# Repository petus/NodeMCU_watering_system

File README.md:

# NodeMCU_watering_system
Watering system for a few plants. The main component is WiFi module NodeMCU with ESP12E (ESP8266).<br>
The device contains two switching parts for pump/valve or another device. <br>
<br>
Websites:<br>
(CZ) https://chiptron.cz<br>
(EN) https://time4ee.com<br>
<br>
Important components: <br>
Relays (Coil Resistance 500 ohm, Nominal Coil Voltage 5 VDC, Switching Voltage 200 VDC, Switching Current 0.5 A) https://www.gme.cz/data/attachments/dsh.634-072.1.pdf <br>
<br>
Transistors (Ultra Low On-Resistance, N-Channel MOSFET, using for switching from GPIO) https://www.infineon.com/dgdl/irlml2502.pdf?fileId=5546d462533600a401535667f44d2602<br>
<br>
Description of device:<br>
NodeMCU watering system includes two outputs (through relays), it can switch water pump, valve or another device. NodeMCU contains one analog input for measurement of soil moisture.<br>
The device contains pin header for connecting of temperature/humidity sensor (by I2C) like Si7021, two LEDs which can be used for indication.<br>
The watering system can be powered by external power supply (the board contains 7805 voltage regulator).<br>

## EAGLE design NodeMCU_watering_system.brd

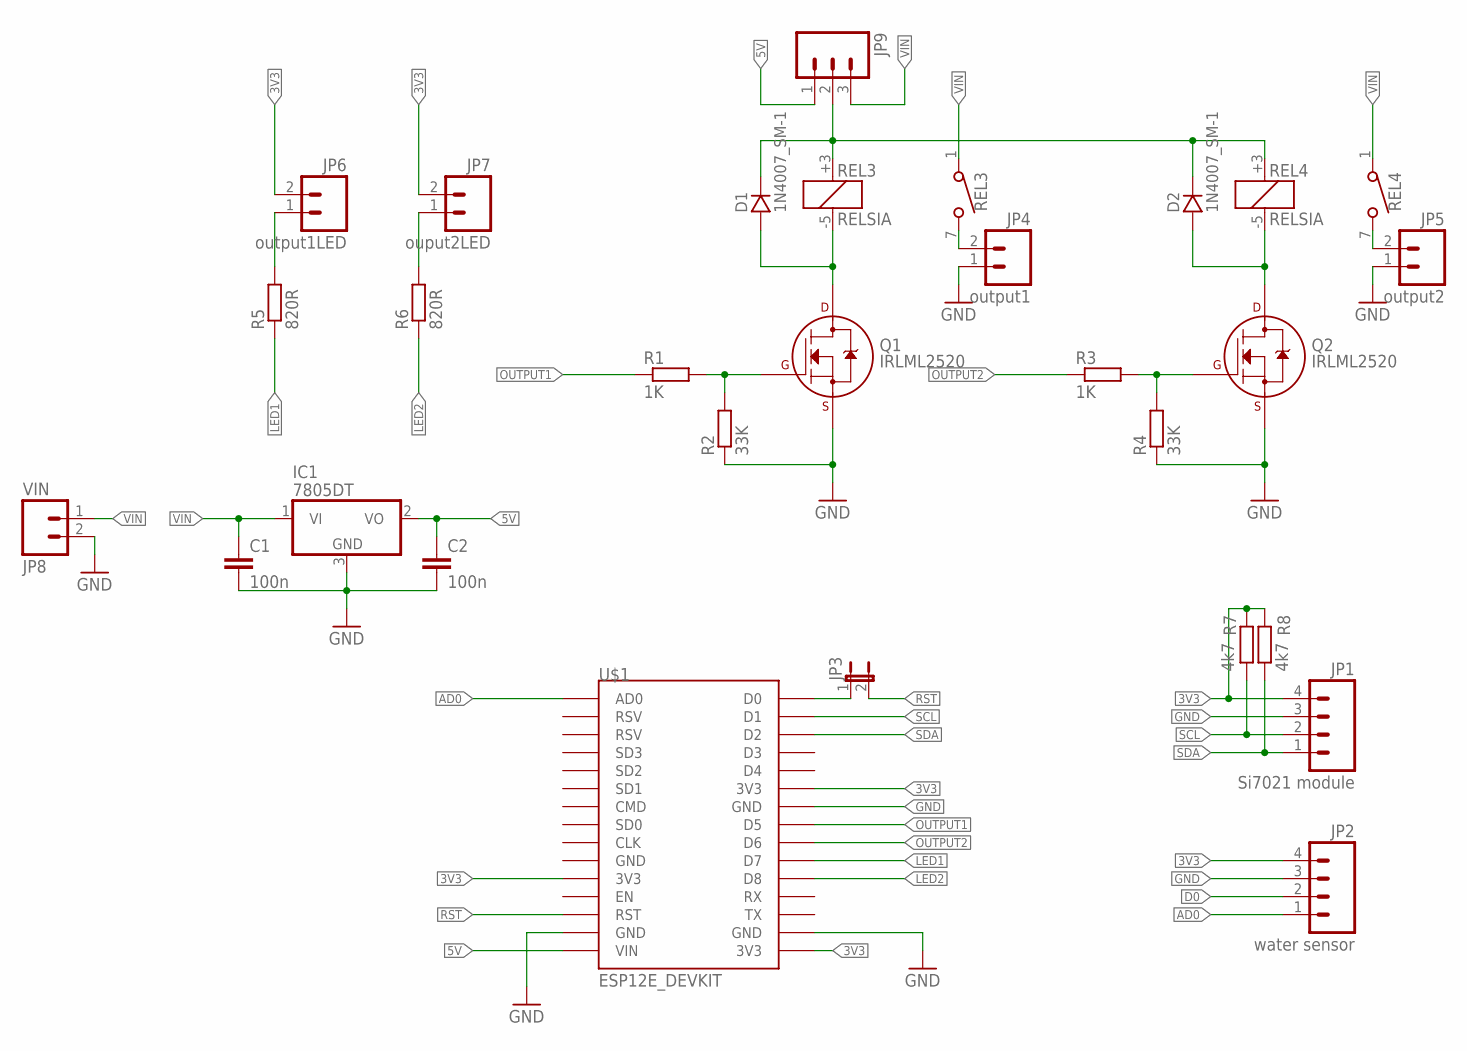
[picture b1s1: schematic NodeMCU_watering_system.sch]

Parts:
C1, C2: 100n; C0805K
D1, D2: 1N4007_SM-1; SM-1
IC1: 7805DT; TO252
JP1: Si7021 module; 1X04_LONGPADS
JP2: water sensor; 1X04_LONGPADS
JP3: JP1E; JP1
JP4: output1; 1X02_LOCK_LONGPADS
JP5: output2; 1X02_LOCK_LONGPADS
JP6: output1LED; 1X02_LOCK_LONGPADS
JP7: ouput2LED; 1X02_LOCK_LONGPADS
JP8: VIN; 1X02_LOCK_LONGPADS
JP9: M03LONGPADS; 1X03_LONGPADS
Q1, Q2: IRLML2520; SOT-23
R1, R3: 1K; M0805
R2, R4: 33K; M0805
R5, R6: 820R; M0805
R7, R8: 4k7; M0805
REL3, REL4: RELSIA
U$1: ESP12E_DEVKIT

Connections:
3V3: JP1.4, JP2.4, JP6.2, JP7.2, R7.2, R8.2, U$1.3V3@0 (3V3), U$1.3V3@1 (3V3), U$1.3V3@2 (3V3)
5V: C2.1, IC1.2 (VO), JP9.1, U$1.VIN
AD0: JP2.1, U$1.AD0
D0: JP2.2
GND: C1.2, C2.2, IC1.3 (GND), JP1.3, JP2.3, JP4.1, JP5.1, JP8.2, Q1.2 (S), Q2.2 (S), R2.1, R4.1, U$1.GND@1 (GND), U$1.GND@2 (GND), U$1.GND@3 (GND)
LED1: R5.1, U$1.D7
LED2: R6.1, U$1.D8
unnamed: JP3.1, U$1.D0
unnamed: Q1.1 (G), R1.2, R2.2
unnamed: Q2.1 (G), R3.2, R4.2
unnamed: D1.A, Q1.3 (D), REL3.-5 (C-)
unnamed: D2.A, Q2.3 (D), REL4.-5 (C-)
unnamed: JP4.2, REL3.7 (2)
unnamed: JP5.2, REL4.7 (2)
unnamed: JP6.1, R5.2
unnamed: JP7.1, R6.2
unnamed: D1.K, D2.K, JP9.2, REL3.+3 (C+), REL4.+3 (C+)
OUTPUT1: R1.1, U$1.D5
OUTPUT2: R3.1, U$1.D6
RST: JP3.2, U$1.RST
SCL: JP1.2, R7.1, U$1.D1
SDA: JP1.1, R8.1, U$1.D2
VIN: C1.1, IC1.1 (VI), JP8.1, JP9.3, REL3.1, REL4.1

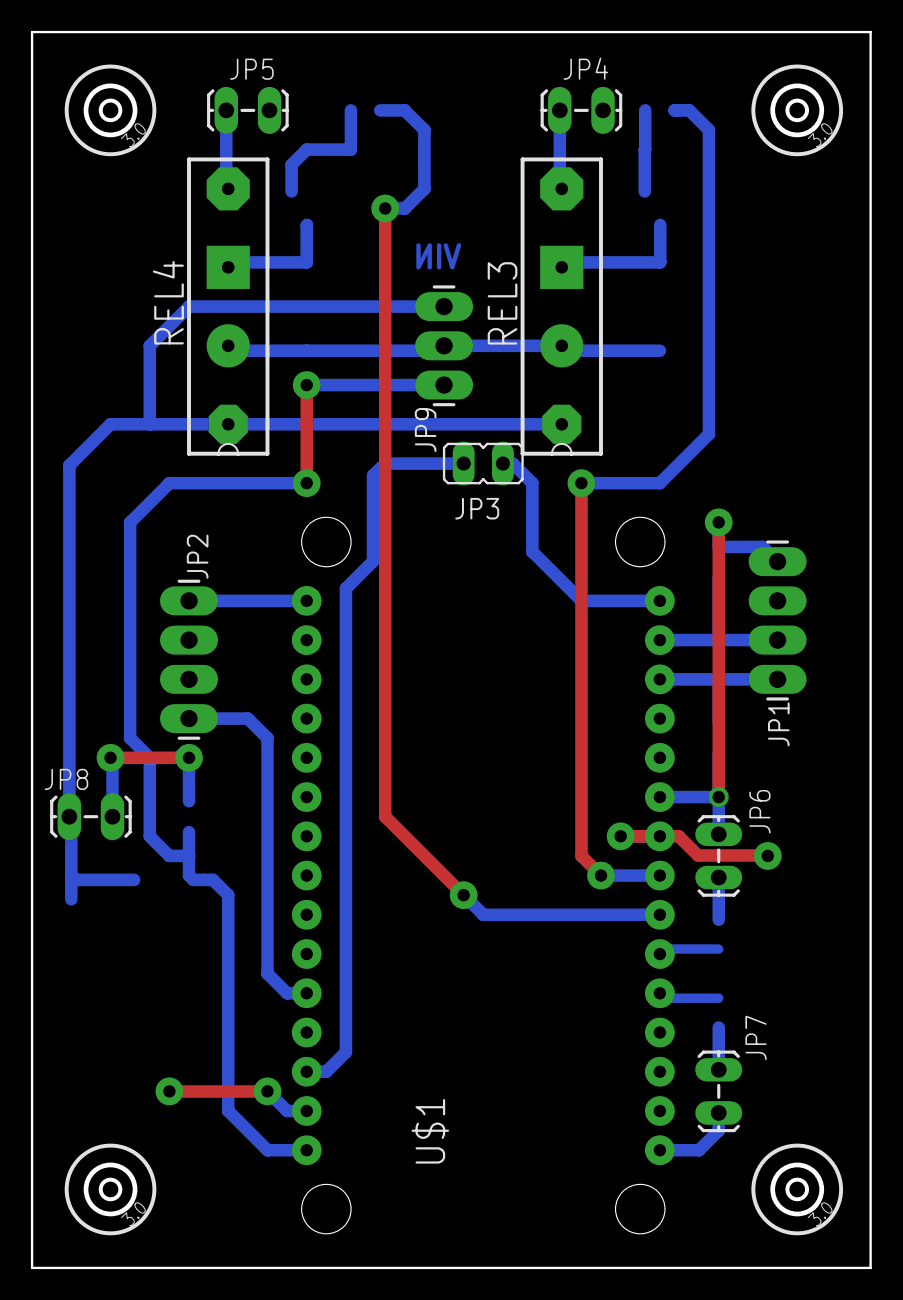
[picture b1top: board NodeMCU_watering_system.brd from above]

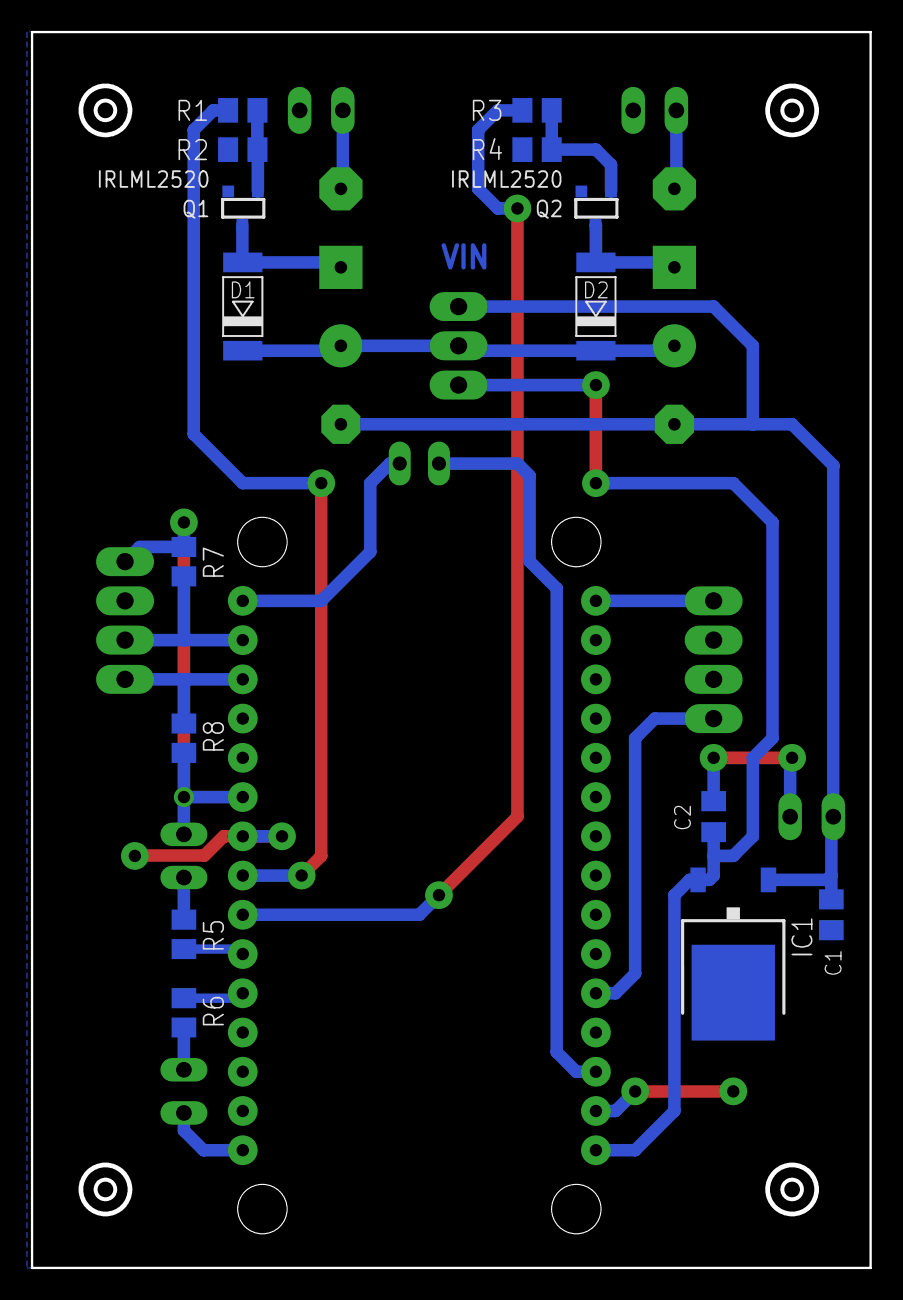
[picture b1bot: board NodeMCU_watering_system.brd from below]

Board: 2 copper layers, 54.1 x 79.8 mm, 31 parts (15 on the bottom side), 22 nets.

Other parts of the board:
U$2, U$3, U$4, U$5: HOLE_3,0

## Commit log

2017-06-07 Add files via upload
    These files are not tested!

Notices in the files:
parts and their libraries:
Copyright (C) PaJa 2001-2011
SparkFun: Licensing: CC v3.0 Share-Alike You are welcome to use this library for commercial purposes.
Copyright (C) PaJa 2001-2010
